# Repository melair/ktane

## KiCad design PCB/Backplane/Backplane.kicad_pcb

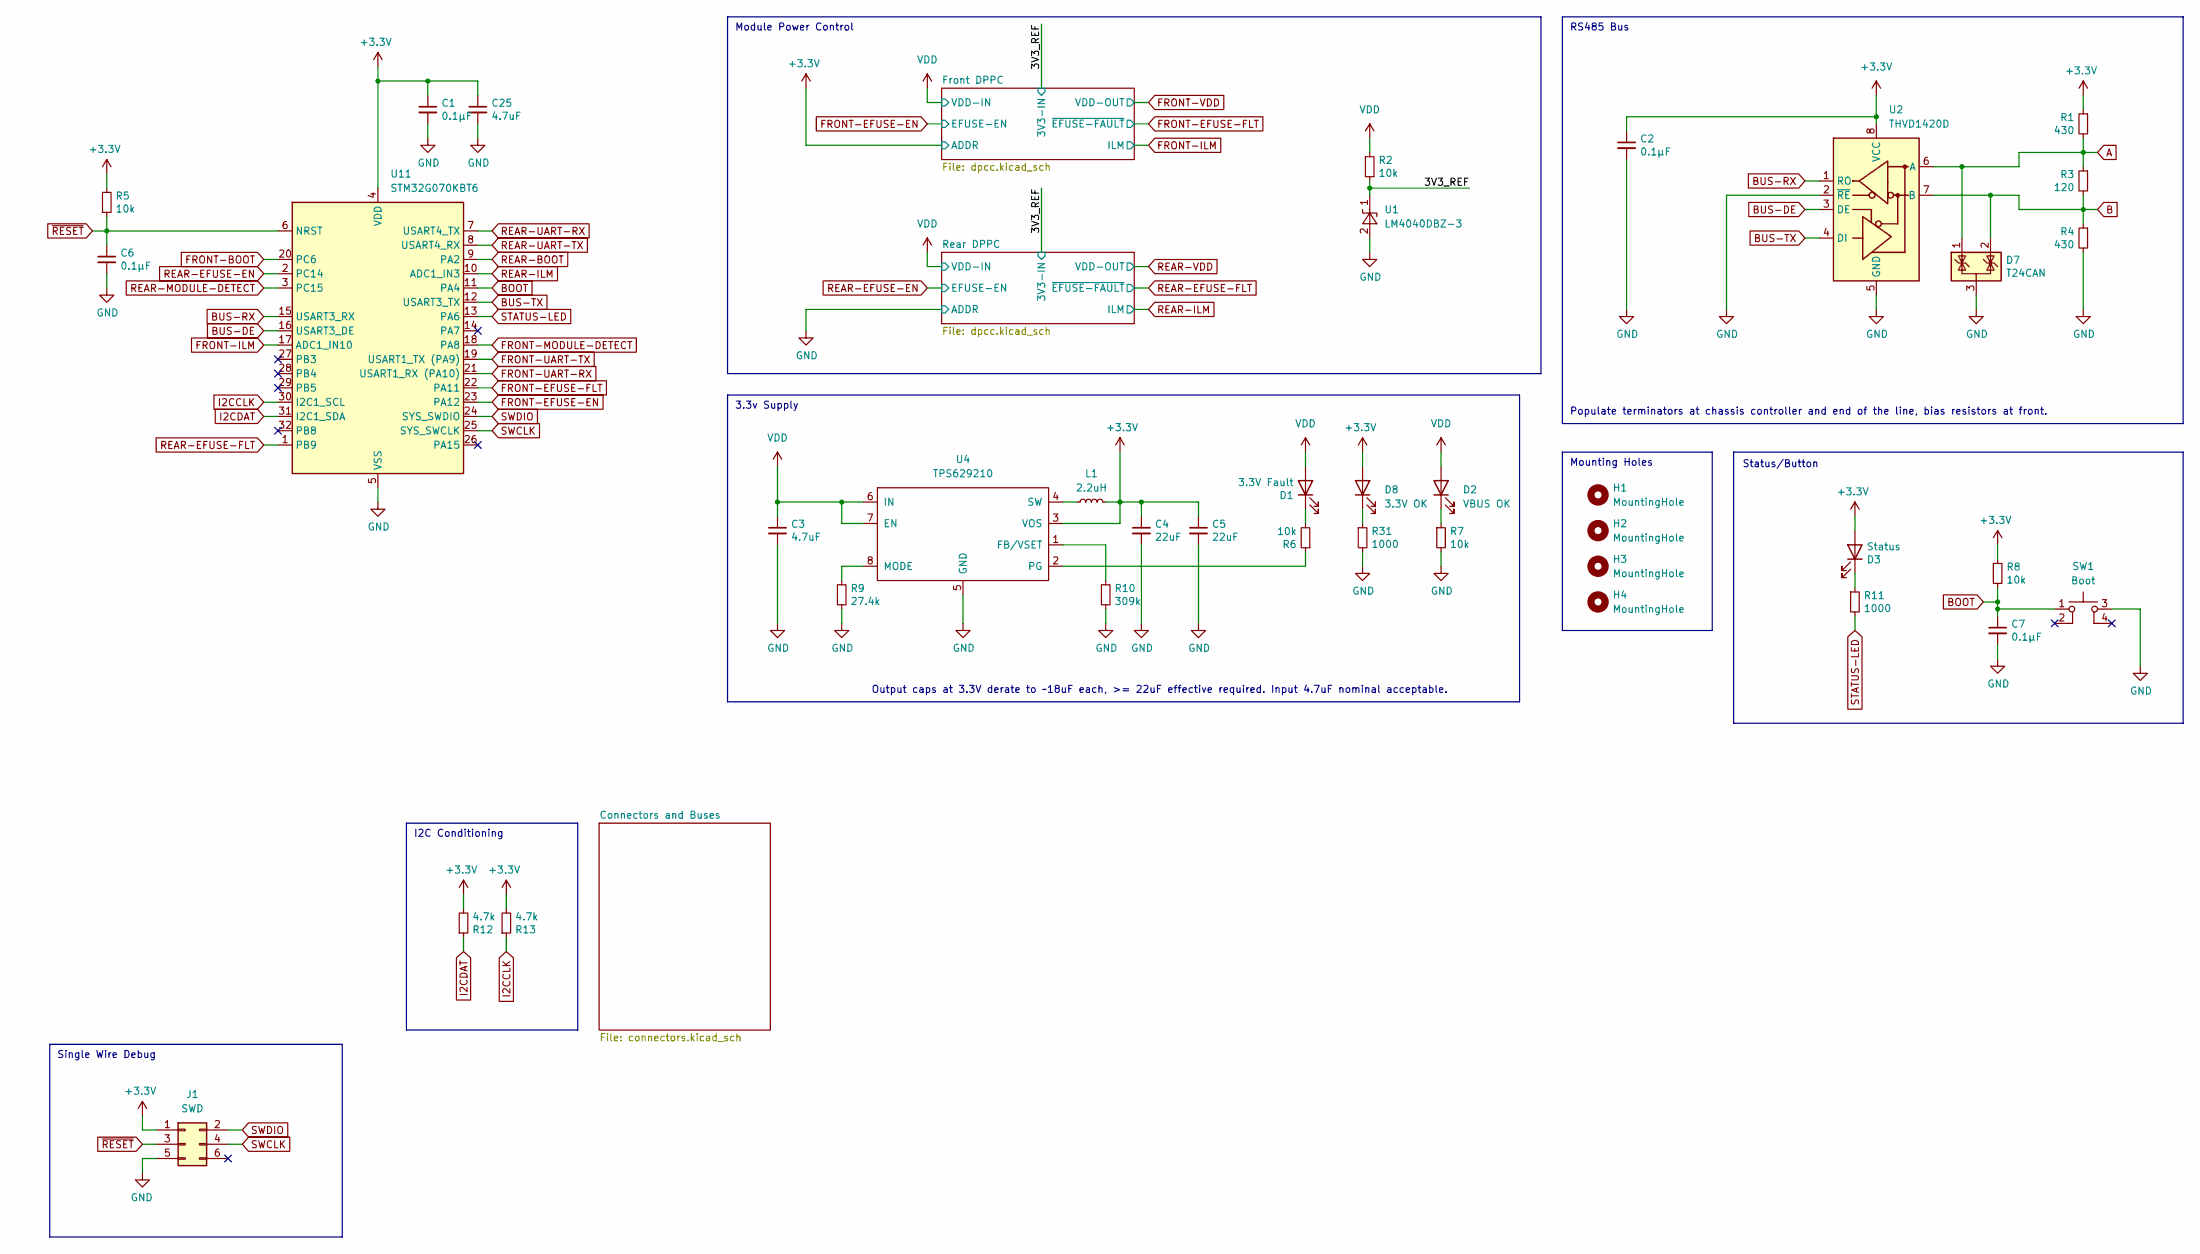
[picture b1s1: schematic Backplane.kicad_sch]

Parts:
C1, C2, C6, C7: 0.1μF; C_0603_1608Metric; DIGIKEY 1276-1005-1-ND
C3: 4.7uF; C_1206_3216Metric; DIGIKEY 445-1606-1-ND
C4, C5: 22uF; C_1206_3216Metric; DIGIKEY 1276-3148-1-ND
C25: 4.7uF; C_0603_1608Metric; DIGIKEY 1276-2087-1-ND
D1: 3.3V Fault; LED_0603_1608Metric; DIGIKEY 3147-B19Y1USD-20C000113U1930CT-ND
D2: VBUS OK; LED_0603_1608Metric; DIGIKEY 3147-B19Y1USD-20C000113U1930CT-ND
D3: Status; LED_0603_1608Metric; DIGIKEY 3147-B19Y1UYG-20C000313U1930CT-ND
D7: T24CAN; SOT-23; DIGIKEY CDSOT23-T24CANCT-ND
D8: 3.3V OK; LED_0603_1608Metric; DIGIKEY 3147-B19Y1UYG-20C000313U1930CT-ND
H1, H2, H3, H4: MountingHole; MountingHole_3.2mm_M3_NoCopper; DIGIKEY NONE
J1: SWD; Tag-Connect_TC2030-IDC-NL_2x03_P1.27mm_Vertical; DIGIKEY NONE
L1: 2.2uH; L_1008_2520Metric; DIGIKEY 490-DFE252012PD-2R2M=P2CT-ND
R1, R4: 430; R_0603_1608Metric; DIGIKEY P430HCT-ND
R2, R5, R6, R7, R8: 10k; R_0603_1608Metric; DIGIKEY P10.0KHCT-ND
R3: 120; R_0603_1608Metric; DIGIKEY P120HCT-ND
R9: 27.4k; R_0603_1608Metric; DIGIKEY P27.4KHCT-ND
R10: 309k; R_0603_1608Metric; DIGIKEY P309KHCT-ND
R11: 1000; R_0603_1608Metric; DIGIKEY P1.00KHCT-ND
R12, R13: 4.7k; R_0603_1608Metric; DIGIKEY P4.7KHCT-ND
R31: 1000; R_0603_1608Metric; DIGIKEY P1.0KHCT-ND
SW1: Boot; PTS526Sx15SMTR2xLFS; DIGIKEY CKN12220-1-ND
U1: LM4040DBZ-3; SOT-23; DIGIKEY 31-LM4040C33FTACT-ND
U2: THVD1420D; SOT-583-8; DIGIKEY 296-THVD1420DRLRCT-ND
U4: TPS629210; SOT-583-8; DIGIKEY 296-TPS629210DRLRCT-ND
U11: STM32G070KBT6; LQFP-32_7x7mm_P0.8mm; DIGIKEY 497-STM32G070KBT6-ND

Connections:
+3.3V: C1.1, C2.1, C4.1, C5.1, C25.1, D3.2 (A), D8.2 (A), J1.1, L1.2, R1.1, R5.1, R8.1, R12.2, R13.2, U2.8 (VCC), U4.3 (VOS), U11.4 (VDD); also elsewhere on the board
/3V3_REF: R2.2, U1.1 (K); also elsewhere on the board
A: D7.1 (K), R1.2, R3.1, U2.6 (A); also elsewhere on the board
B: D7.2 (K), R3.2, R4.1, U2.7 (B); also elsewhere on the board
BOOT: C7.1, R8.2, SW1.1, U11.11 (PA4)
BUS-DE: U2.3 (DE), U11.16 (USART3_DE)
BUS-RX: U2.1 (RO), U11.15 (USART3_RX)
BUS-TX: U2.4 (DI), U11.12 (USART3_TX)
FRONT-BOOT: U11.20 (PC6); also elsewhere on the board
FRONT-EFUSE-EN: U11.23 (PA12); also elsewhere on the board
FRONT-EFUSE-FLT: U11.22 (PA11); also elsewhere on the board
FRONT-ILM: U11.17 (ADC1_IN10); also elsewhere on the board
FRONT-MODULE-DETECT: U11.18 (PA8); also elsewhere on the board
FRONT-UART-RX: U11.21 (USART1_RX (PA10)); also elsewhere on the board
FRONT-UART-TX: U11.19 (USART1_TX (PA9)); also elsewhere on the board
GND: C1.2, C2.2, C3.2, C4.2, C5.2, C6.2, C7.2, C25.2, D7.3 (A), J1.5, R4.2, R7.2, R9.2, R10.2, R31.2, SW1.3, U1.2 (A), U2.2 (~RE), U2.5 (GND), U4.5 (GND), U11.5 (VSS); also elsewhere on the board
I2CCLK: R13.1, U11.30 (I2C1_SCL); also elsewhere on the board
I2CDAT: R12.1, U11.31 (I2C1_SDA); also elsewhere on the board
unnamed: D1.1 (K), R6.2
unnamed: D2.1 (K), R7.1
unnamed: D3.1 (K), R11.1
unnamed: D8.1 (K), R31.1
unnamed: R10.1, U4.1 (FB/VSET)
unnamed: R9.1, U4.8 (MODE)
unnamed: R6.1, U4.2 (PG)
unnamed: L1.1, U4.4 (SW)
REAR-BOOT: U11.9 (PA2); also elsewhere on the board
REAR-EFUSE-EN: U11.2 (PC14); also elsewhere on the board
REAR-EFUSE-FLT: U11.1 (PB9); also elsewhere on the board
REAR-ILM: U11.10 (ADC1_IN3); also elsewhere on the board
REAR-MODULE-DETECT: U11.3 (PC15); also elsewhere on the board
REAR-UART-RX: U11.7 (USART4_TX); also elsewhere on the board
REAR-UART-TX: U11.8 (USART4_RX); also elsewhere on the board
STATUS-LED: R11.2, U11.13 (PA6)
SWCLK: J1.4, U11.25 (SYS_SWCLK)
SWDIO: J1.2, U11.24 (SYS_SWDIO)
VDD: C3.1, D1.2 (A), D2.2 (A), R2.1, U4.6 (IN), U4.7 (EN); also elsewhere on the board
~RESET: C6.1, J1.3, R5.2, U11.6 (NRST)

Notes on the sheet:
I2C Conditioning
Module Power Control
Single Wire Debug
Output caps at 3.3V derate to ~18uF each, >= 22uF effective required. Input 4.7uF nominal acceptable.
Status/Button
Mounting Holes
3.3v Supply
Populate terminators at chassis controller and end of the line, bias resistors at front.
RS485 Bus

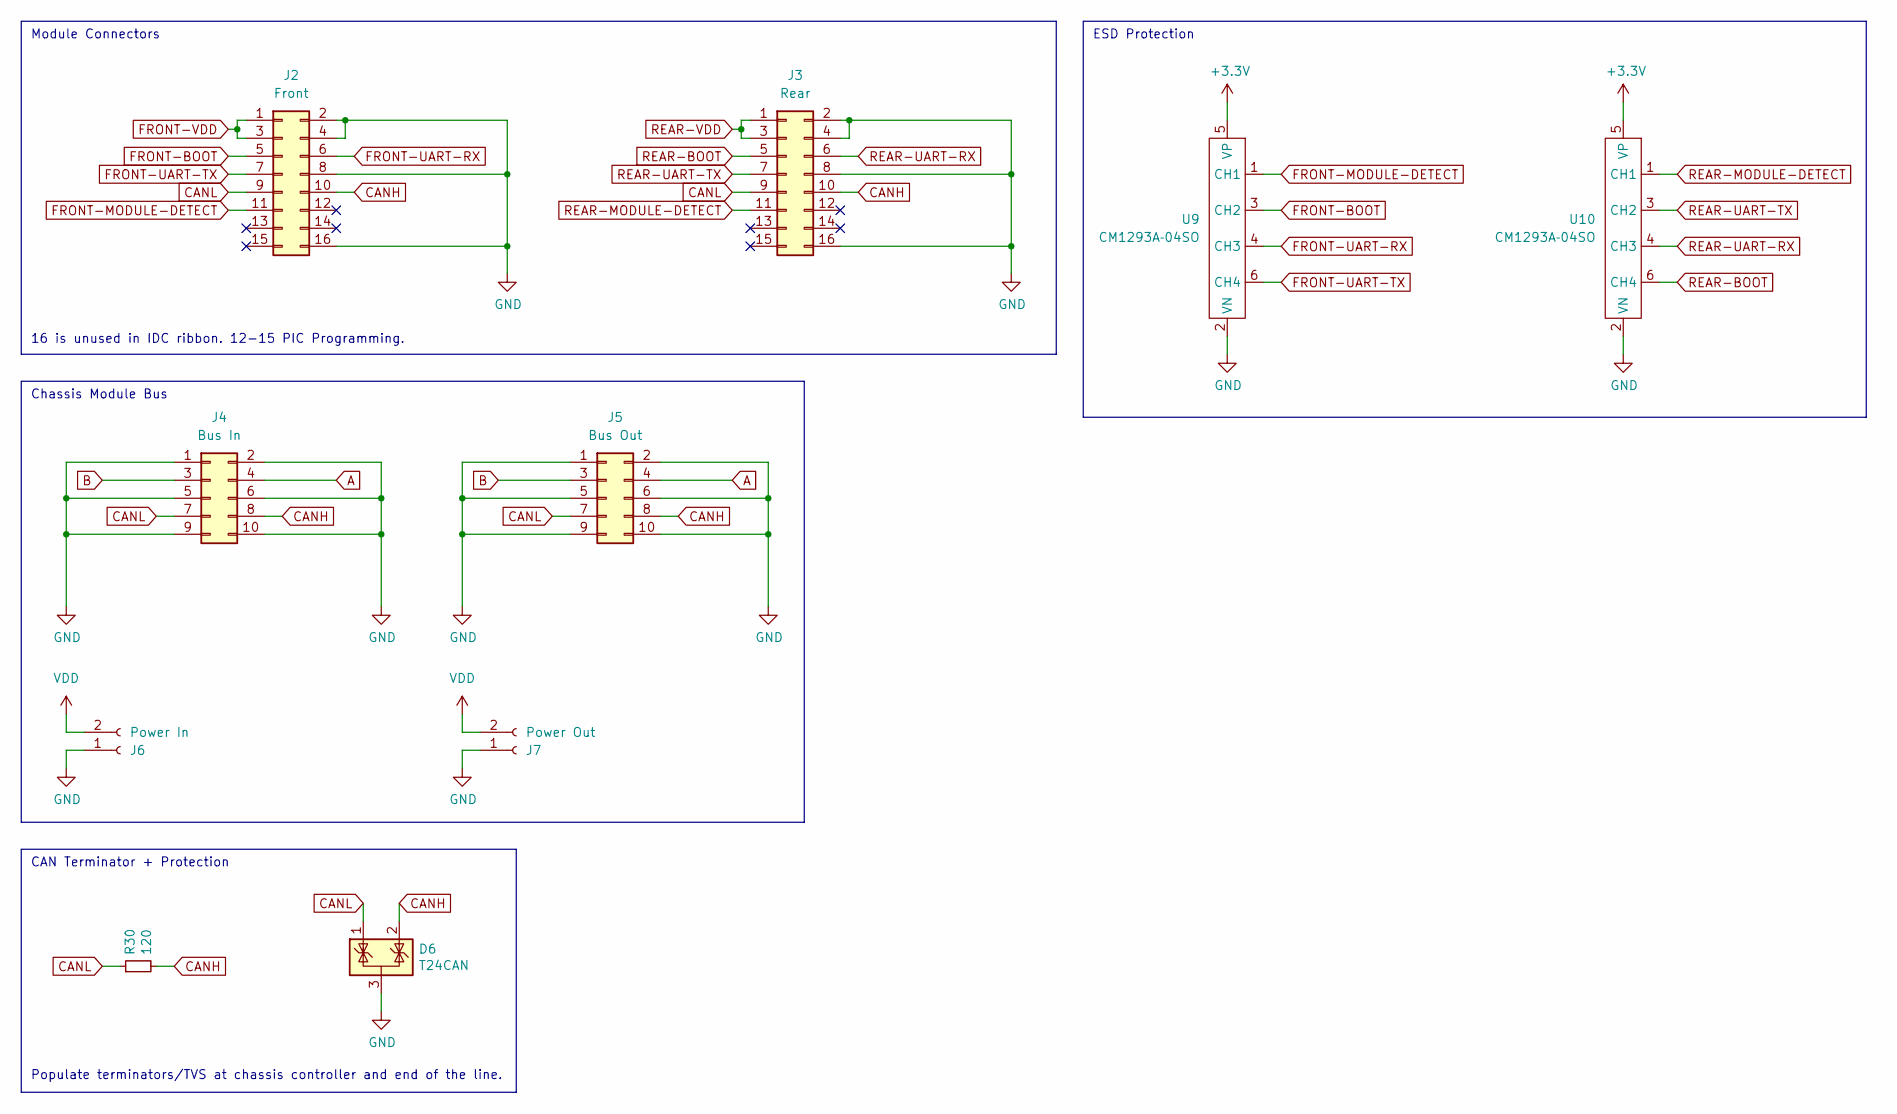
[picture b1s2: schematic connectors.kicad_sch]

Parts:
D6: T24CAN; SOT-23; DIGIKEY CDSOT23-T24CANCT-ND
J2: Front; PinHeader_2x08_P2.54mm_VerticalAndHorizontal_Centered; DIGIKEY STOCK/Toby
J3: Rear; PinHeader_2x08_P2.54mm_VerticalAndHorizontal_Centered; DIGIKEY STOCK/Toby
J4: Bus In; PinHeader_2x05_P2.54mm_VerticalAndHorizontal_Centered; DIGIKEY STOCK/Toby
J5: Bus Out; PinHeader_2x05_P2.54mm_VerticalAndHorizontal_Centered; DIGIKEY STOCK/Toby
J6: Power In; AMASS_XT30PW-M_1x02_P2.50mm_Horizontal; DIGIKEY STOCK/ALIEXPRESS
J7: Power Out; AMASS_XT30PW-F_1x02_P2.50mm_Horizontal; DIGIKEY STOCK/ALIEXPRESS
R30: 120; R_0603_1608Metric; DIGIKEY P120HCT-ND
U9, U10: CM1293A‐04SO; SC-74-6_1.55x2.9mm_P0.95mm; DIGIKEY CM1293A-04SOOSCT-ND

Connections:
+3.3V: U9.5 (VP), U10.5 (VP); also elsewhere on the board
A: J4.4, J5.4; also elsewhere on the board
B: J4.3, J5.3; also elsewhere on the board
CANH: D6.2 (K), J2.10, J3.10, J4.8, J5.8, R30.2
CANL: D6.1 (K), J2.9, J3.9, J4.7, J5.7, R30.1
FRONT-BOOT: J2.5, U9.3 (CH2); also elsewhere on the board
FRONT-MODULE-DETECT: J2.11, U9.1 (CH1); also elsewhere on the board
FRONT-UART-RX: J2.6, U9.4 (CH3); also elsewhere on the board
FRONT-UART-TX: J2.7, U9.6 (CH4); also elsewhere on the board
FRONT-VDD: J2.1, J2.3; also elsewhere on the board
GND: D6.3 (A), J2.2, J2.4, J2.8, J2.16, J3.2, J3.4, J3.8, J3.16, J4.1, J4.2, J4.5, J4.6, J4.9, J4.10, J5.1, J5.2, J5.5, J5.6, J5.9, J5.10, J6.1, J7.1, U9.2 (VN), U10.2 (VN); also elsewhere on the board
REAR-BOOT: J3.5, U10.6 (CH4); also elsewhere on the board
REAR-MODULE-DETECT: J3.11, U10.1 (CH1); also elsewhere on the board
REAR-UART-RX: J3.6, U10.4 (CH3); also elsewhere on the board
REAR-UART-TX: J3.7, U10.3 (CH2); also elsewhere on the board
REAR-VDD: J3.1, J3.3; also elsewhere on the board
VDD: J6.2, J7.2; also elsewhere on the board

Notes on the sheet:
Chassis Module Bus
Module Connectors
CAN Terminator + Protection
16 is unused in IDC ribbon. 12-15 PIC Programming.
Populate terminators/TVS at chassis controller and end of the line.
ESD Protection

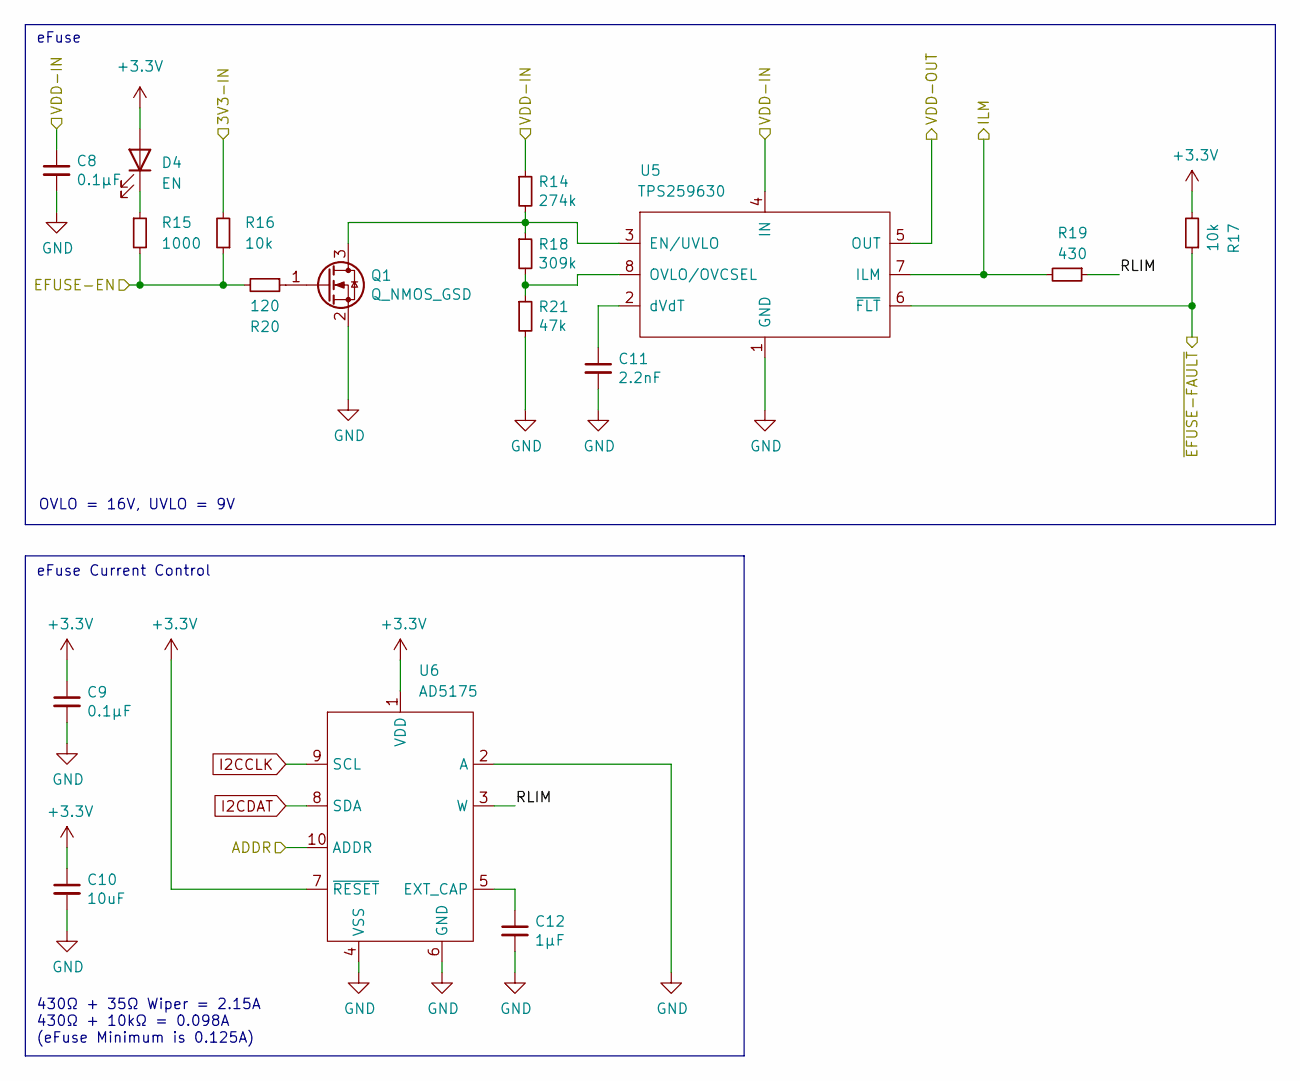
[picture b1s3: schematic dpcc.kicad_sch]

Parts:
C8, C9: 0.1μF; C_0603_1608Metric; DIGIKEY 1276-1005-1-ND
C10: 10uF; C_0603_1608Metric; DIGIKEY 1276-1948-1-ND
C11: 2.2nF; C_0603_1608Metric; DIGIKEY 1276-6530-1-ND
C12: 1μF; C_0603_1608Metric; DIGIKEY 1276-1946-1-ND
D4: EN; LED_0603_1608Metric; DIGIKEY 3147-B19Y1USD-20C000113U1930CT-ND
Q1: Q_NMOS_GSD; SOT-23; DIGIKEY 31-DMN2310U-7CT-ND
R14: 274k; R_0603_1608Metric; DIGIKEY P274KHCT-ND
R15: 1000; R_0603_1608Metric; DIGIKEY P1.00KHCT-ND
R16, R17: 10k; R_0603_1608Metric; DIGIKEY P10.0KHCT-ND
R18: 309k; R_0603_1608Metric; DIGIKEY P309KHCT-ND
R19: 430; R_0603_1608Metric; DIGIKEY P430HCT-ND
R20: 120; R_0603_1608Metric; DIGIKEY P120HCT-ND
R21: 47k; R_0603_1608Metric; DIGIKEY P47.0KHCT-ND
U5: TPS259630; SOIC-8-1EP_3.9x4.9mm_P1.27mm_EP2.29x3mm; DIGIKEY 296-TPS259631DDARCT-ND
U6: AD5175; MSOP-10_3x3mm_P0.5mm; DIGIKEY 505-AD5175BRMZ-10-ND

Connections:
+3.3V: C9.1, C10.1, D4.2 (A), R17.2, U6.1 (VDD), U6.7 (~RESET), U6.10 (ADDR); also elsewhere on the board
/3V3_REF: R16.2; also elsewhere on the board
/Front DPPC/RLIM: R19.1, U6.3 (W)
FRONT-EFUSE-EN: R15.2, R16.1, R20.2; also elsewhere on the board
FRONT-EFUSE-FLT: R17.1, U5.6 (~FLT); also elsewhere on the board
FRONT-ILM: R19.2, U5.7 (ILM); also elsewhere on the board
FRONT-VDD: U5.5 (OUT); also elsewhere on the board
GND: C8.2, C9.2, C10.2, C11.2, C12.2, Q1.2 (S), R21.2, U5.1 (GND), U5.9 (GND), U6.2 (A), U6.4 (VSS), U6.6 (GND); also elsewhere on the board
I2CCLK: U6.9 (SCL); also elsewhere on the board
I2CDAT: U6.8 (SDA); also elsewhere on the board
unnamed: D4.1 (K), R15.1
unnamed: Q1.3 (D), R14.2, R18.1, U5.3 (EN/UVLO)
unnamed: Q1.1 (G), R20.1
unnamed: R18.2, R21.1, U5.8 (OVLO/OVCSEL)
unnamed: C11.1, U5.2 (dVdT)
unnamed: C12.1, U6.5 (EXT_CAP)
VDD: C8.1, R14.1, U5.4 (IN); also elsewhere on the board

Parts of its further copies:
C13, C14: 0.1μF; C_0603_1608Metric; DIGIKEY 1276-1005-1-ND
C15: 10uF; C_0603_1608Metric; DIGIKEY 1276-1948-1-ND
C16: 2.2nF; C_0603_1608Metric; DIGIKEY 1276-6530-1-ND
C17: 1μF; C_0603_1608Metric; DIGIKEY 1276-1946-1-ND
D5: EN; LED_0603_1608Metric; DIGIKEY 3147-B19Y1USD-20C000113U1930CT-ND
Q2: Q_NMOS_GSD; SOT-23; DIGIKEY 31-DMN2310U-7CT-ND
R22: 274k; R_0603_1608Metric; DIGIKEY P274KHCT-ND
R23: 1000; R_0603_1608Metric; DIGIKEY P1.00KHCT-ND
R24, R25: 10k; R_0603_1608Metric; DIGIKEY P10.0KHCT-ND
R26: 309k; R_0603_1608Metric; DIGIKEY P309KHCT-ND
R27: 430; R_0603_1608Metric; DIGIKEY P430HCT-ND
R28: 120; R_0603_1608Metric; DIGIKEY P120HCT-ND
R29: 47k; R_0603_1608Metric; DIGIKEY P47.0KHCT-ND
U7: TPS259630; SOIC-8-1EP_3.9x4.9mm_P1.27mm_EP2.29x3mm; DIGIKEY 296-TPS259631DDARCT-ND
U8: AD5175; MSOP-10_3x3mm_P0.5mm; DIGIKEY 505-AD5175BRMZ-10-ND

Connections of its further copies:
+3.3V: C14.1, C15.1, D5.2 (A), R25.2, U8.1 (VDD), U8.7 (~RESET); also elsewhere on the board
/3V3_REF: R24.2; also elsewhere on the board
/Rear DPPC/RLIM: R27.1, U8.3 (W)
GND: C13.2, C14.2, C15.2, C16.2, C17.2, Q2.2 (S), R29.2, U7.1 (GND), U7.9 (GND), U8.2 (A), U8.4 (VSS), U8.6 (GND), U8.10 (ADDR); also elsewhere on the board
I2CCLK: U8.9 (SCL); also elsewhere on the board
I2CDAT: U8.8 (SDA); also elsewhere on the board
unnamed: D5.1 (K), R23.1
unnamed: Q2.3 (D), R22.2, R26.1, U7.3 (EN/UVLO)
unnamed: Q2.1 (G), R28.1
unnamed: R26.2, R29.1, U7.8 (OVLO/OVCSEL)
unnamed: C16.1, U7.2 (dVdT)
unnamed: C17.1, U8.5 (EXT_CAP)
REAR-EFUSE-EN: R23.2, R24.1, R28.2; also elsewhere on the board
REAR-EFUSE-FLT: R25.1, U7.6 (~FLT); also elsewhere on the board
REAR-ILM: R27.2, U7.7 (ILM); also elsewhere on the board
REAR-VDD: U7.5 (OUT); also elsewhere on the board
VDD: C13.1, R22.1, U7.4 (IN); also elsewhere on the board

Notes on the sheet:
eFuse
430Ω + 35Ω Wiper = 2.15A 430Ω + 10kΩ = 0.098A (eFuse Minimum is 0.125A)
OVLO = 16V, UVLO = 9V
eFuse Current Control

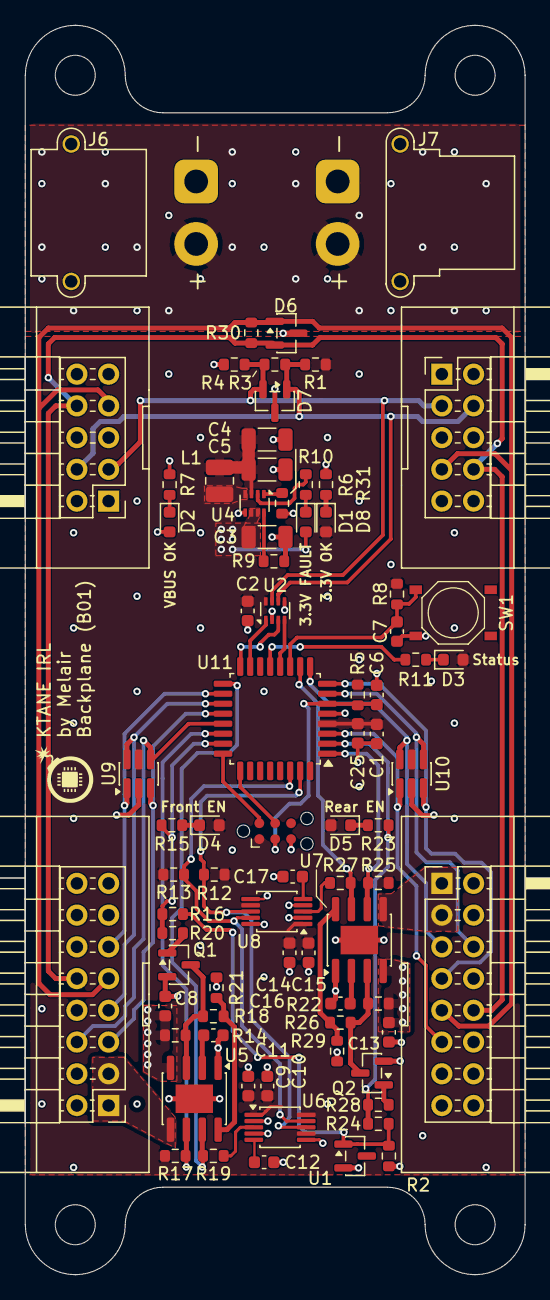
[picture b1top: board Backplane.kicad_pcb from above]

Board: 4 copper layers, 40.0 x 100.0 mm, 82 parts (0 on the bottom side), 56 nets.

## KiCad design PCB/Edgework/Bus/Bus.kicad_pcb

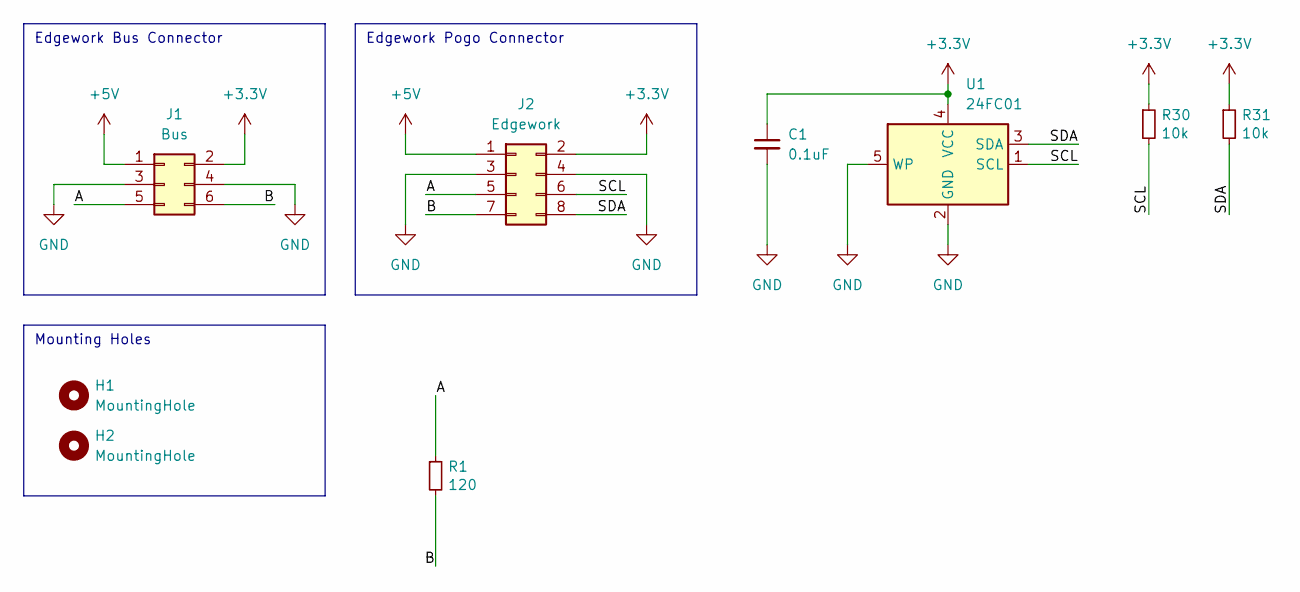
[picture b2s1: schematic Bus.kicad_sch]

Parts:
C1: 0.1uF; C_0603_1608Metric; DIGIKEY 1276-1005-1-ND
H1, H2: MountingHole; MountingHole_3.2mm_M3; DIGIKEY NONE
J1: Bus; PinHeader_2x03_P2.54mm_Horizontal; DIGIKEY STOCK
J2: Edgework; PinHeader_2x04_P2.54mm_Vertical; DIGIKEY STOCK
R1: 120; R_0603_1608Metric; DIGIKEY P120HCT-ND
R30, R31: 10k; R_0603_1608Metric; DIGIKEY P10.0KHCT-ND
U1: 24FC01; SOT-23-5; DIGIKEY 24FC01T-I/OTCT-ND

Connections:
+3.3V: C1.1, J1.2, J2.2, R30.1, R31.1, U1.4 (VCC)
+5V: J1.1, J2.1
/A: J1.5, J2.5, R1.1
/B: J1.6, J2.7, R1.2
/SCL: J2.6, R30.2, U1.1 (SCL)
/SDA: J2.8, R31.2, U1.3 (SDA)
GND: C1.2, J1.3, J1.4, J2.3, J2.4, U1.2 (GND), U1.5 (WP)

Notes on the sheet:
Edgework Bus Connector
Edgework Pogo Connector
Mounting Holes

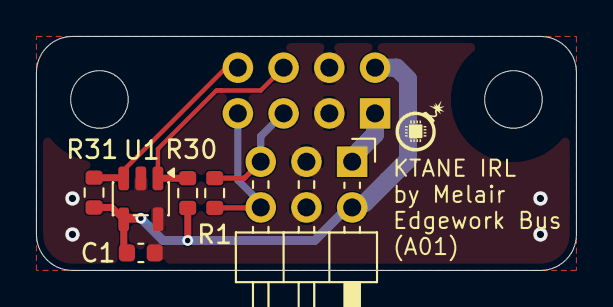
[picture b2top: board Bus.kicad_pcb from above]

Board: 2 copper layers, 30.0 x 13.0 mm, 9 parts (1 on the bottom side), 7 nets.

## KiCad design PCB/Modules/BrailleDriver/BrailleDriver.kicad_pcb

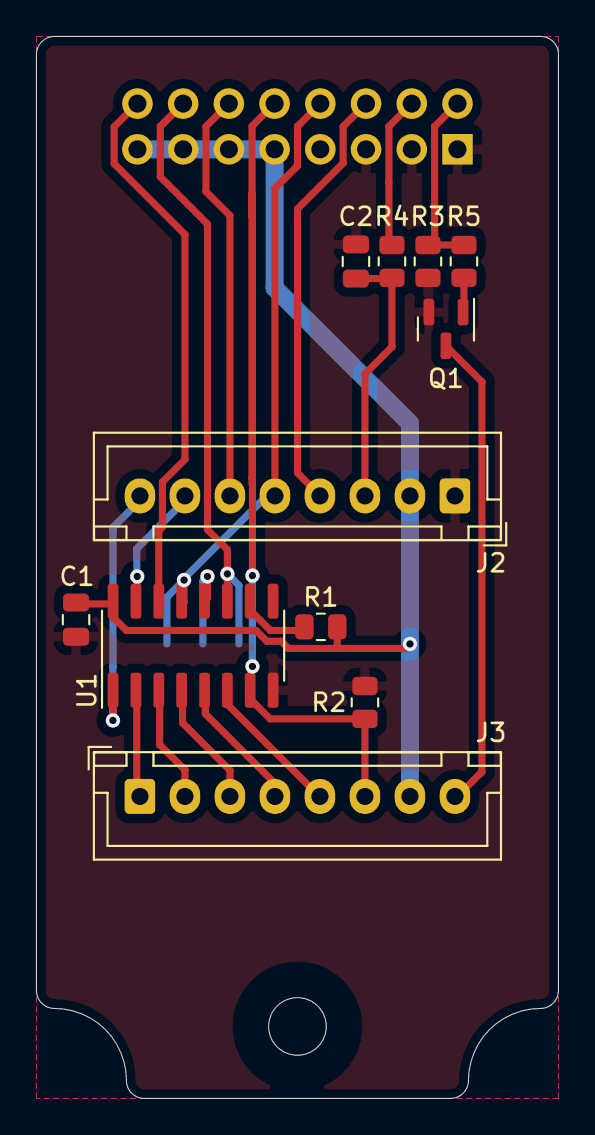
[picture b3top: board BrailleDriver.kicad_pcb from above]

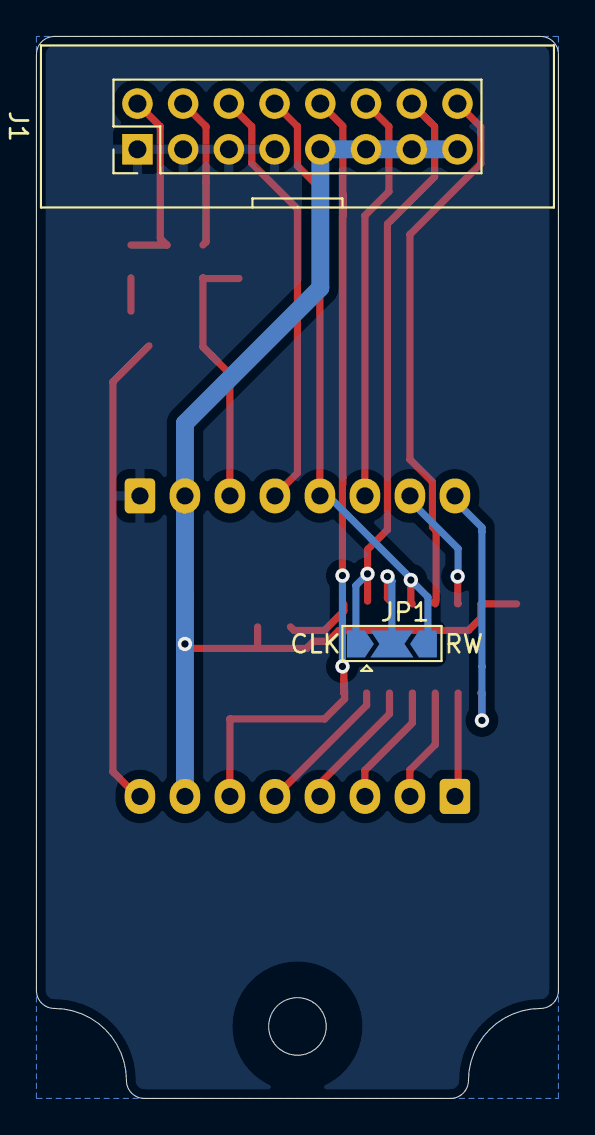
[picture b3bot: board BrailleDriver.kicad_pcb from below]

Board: 2 copper layers, 29.0 x 59.0 mm, 13 parts (2 on the bottom side), 22 nets.

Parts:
C1: 10uF; C_0805_2012Metric
C2: 22uF; C_0805_2012Metric
J1: In; PinHeader_2x08_P2.54mm_Vertical-Centered
J2, J3: Conn_01x08; JST_XH_B8B-XH-A_1x08_P2.50mm_Vertical
JP1: Jumper_3_Open; SolderJumper-3_P2.0mm_Open_TrianglePad1.0x1.5mm
Q1: Q_NMOS_GSD; SOT-23
R1, R2: 10k; R_0805_2012Metric
R3: 47k; R_0805_2012Metric
R4: 1k; R_0805_2012Metric
R5: 120; R_0805_2012Metric
U1: 74HC595; SOIC-16_3.9x9.9mm_P1.27mm

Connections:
+5V: C1.1, J1.9, J1.11, J1.13, J1.15, J2.2, J3.7, R1.2, U1.16 (VCC)
/D0: J2.7, U1.15 (QA)
/D1: J2.8, U1.1 (QB)
/D2: J3.1, U1.2 (QC)
/D3: J3.2, U1.3 (QD)
/D4: J3.3, U1.4 (QE)
/D5: J3.4, U1.5 (QF)
/D6: J3.5, U1.6 (QG)
CLK: J1.14, JP1.1 (A), U1.11 (SRCLK)
D7: J1.10, J3.6, R2.2, U1.7 (QH)
DAT: J1.16, U1.14 (SER)
E: J1.12, J2.6
GND: C1.2, C2.2, J1.1, J1.3, J1.5, J1.7, J2.1, Q1.2 (S), R2.1, R3.1, U1.8 (GND)
K: J3.8, Q1.3 (D)
K-SIGNAL: J1.2, R3.2, R5.2
unnamed: Q1.1 (G), R5.1
unnamed: R1.1, U1.10 (~SRCLR)
unnamed: JP1.2 (C), U1.12 (RCLK)
RS: J1.6, J2.4
RW: J1.8, J2.5, JP1.3 (B), U1.13 (~OE)
VO: C2.1, J2.3, R4.1
VO-SIGNAL: J1.4, R4.2

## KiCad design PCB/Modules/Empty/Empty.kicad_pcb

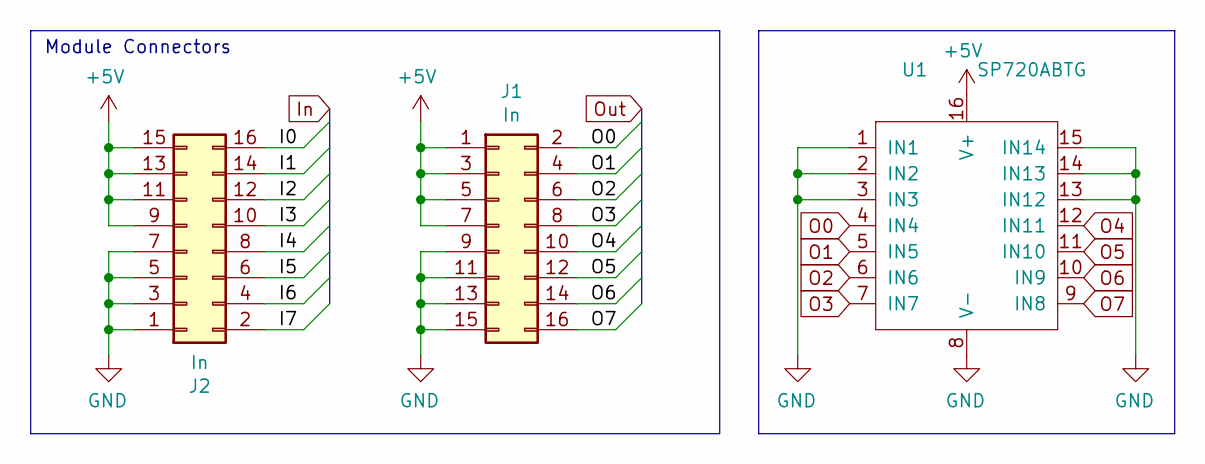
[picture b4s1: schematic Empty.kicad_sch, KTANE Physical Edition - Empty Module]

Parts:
J1, J2: In; PinHeader_2x08_P2.54mm_Vertical-Centered
U1: SP720ABTG; SOIC-16_3.9x9.9mm_P1.27mm

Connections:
+5V: J1.1, J1.3, J1.5, J1.7, J2.9, J2.11, J2.13, J2.15, U1.16 (V+)
GND: J1.9, J1.11, J1.13, J1.15, J2.1, J2.3, J2.5, J2.7, U1.1 (IN1), U1.2 (IN2), U1.3 (IN3), U1.8 (V-), U1.13 (IN12), U1.14 (IN13), U1.15 (IN14)
I0: J2.16
I1: J2.14
I2: J2.12
I3: J2.10
I4: J2.8
I5: J2.6
I6: J2.4
I7: J2.2
O0: J1.2, U1.4 (IN4)
O1: J1.4, U1.5 (IN5)
O2: J1.6, U1.6 (IN6)
O3: J1.8, U1.7 (IN7)
O4: J1.10, U1.12 (IN11)
O5: J1.12, U1.11 (IN10)
O6: J1.14, U1.10 (IN9)
O7: J1.16, U1.9 (IN8)

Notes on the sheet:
Module Connectors

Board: 2 copper layers, 3 parts (1 on the bottom side), 10 nets, no tracks yet.

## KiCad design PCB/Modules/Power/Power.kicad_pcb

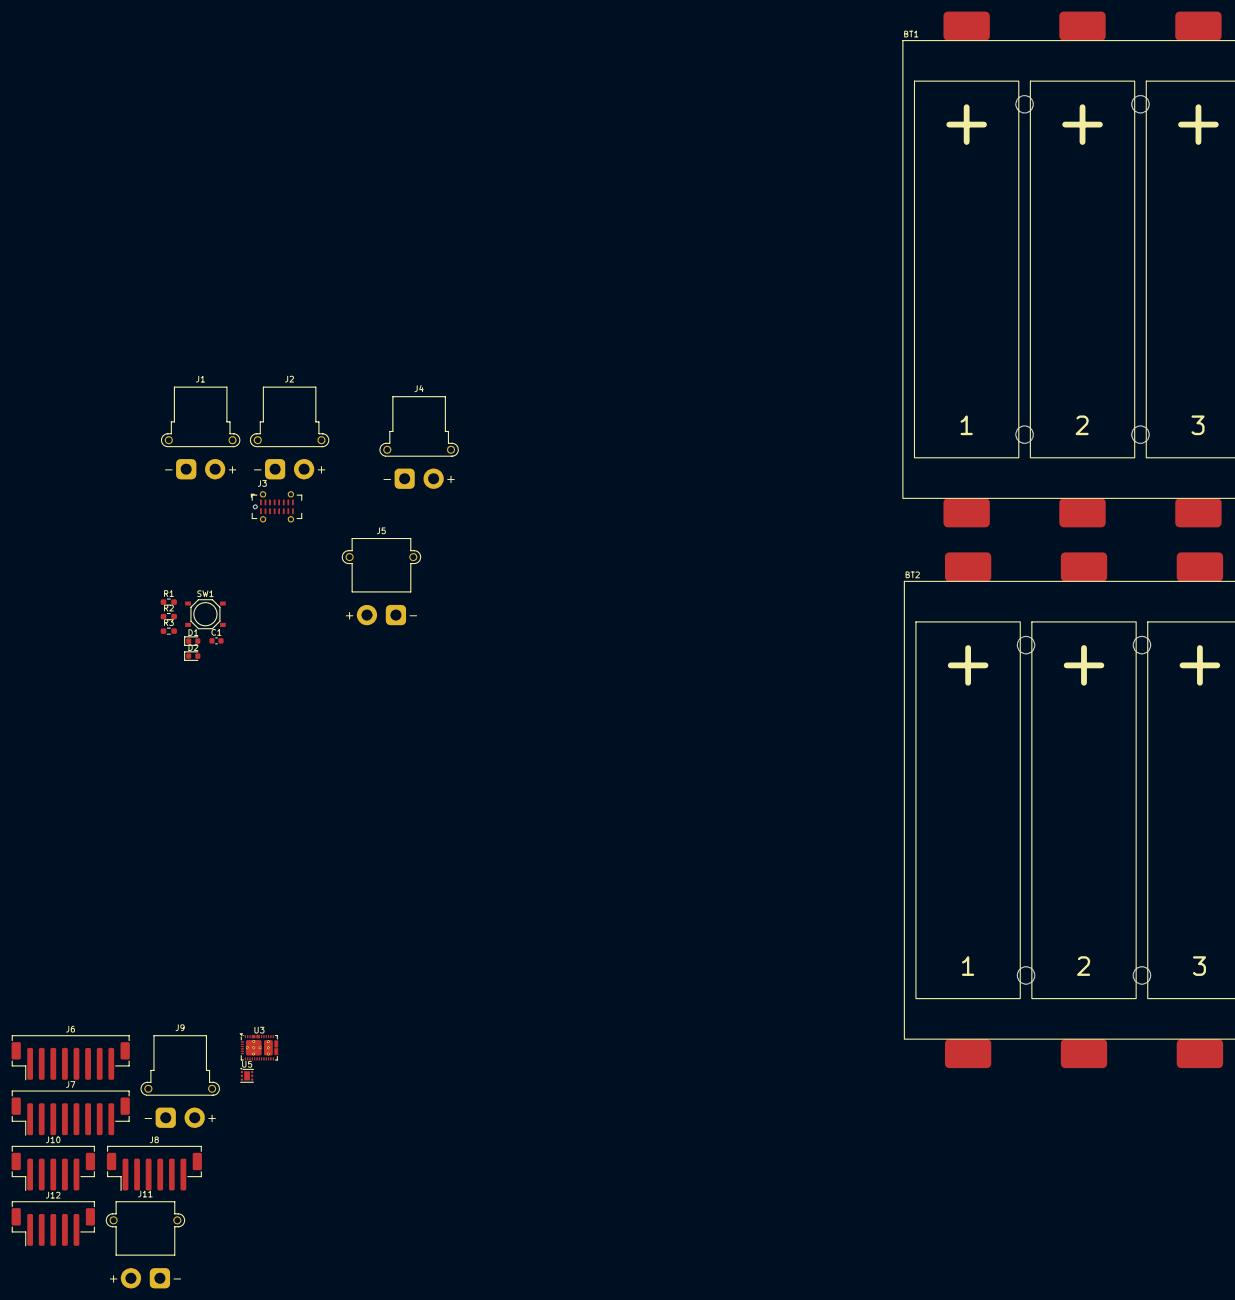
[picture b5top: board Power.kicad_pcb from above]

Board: 2 copper layers, 23 parts (0 on the bottom side), 27 nets, no tracks yet.

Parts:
BT1, BT2: 3Cell18650Holder
C1: 1nF; C_0603_1608Metric
D1: OK; LED_0603_1608Metric
D2: Fault; LED_0603_1608Metric
J1: Out1; AMASS_XT30PW-F_1x02_P2.50mm_Horizontal
J2: Out2; AMASS_XT30PW-F_1x02_P2.50mm_Horizontal
J3: USB_C_Receptacle_USB2.0_14P; USB_C_Receptacle_G-Switch_GT-USB-7051x
J4: VBus; AMASS_XT30PW-F_1x02_P2.50mm_Horizontal
J5: VBus; AMASS_XT30PW-M_1x02_P2.50mm_Horizontal
J6, J7: Comms; JST_PH_B8B-PH-SM4-TB_1x08-1MP_P2.00mm_Vertical
J8: Host; JST_PH_B6B-PH-SM4-TB_1x06-1MP_P2.00mm_Vertical
J9: Battery; AMASS_XT30PW-F_1x02_P2.50mm_Horizontal
J10, J12: Comms; JST_PH_B5B-PH-SM4-TB_1x05-1MP_P2.00mm_Vertical
J11: Battery; AMASS_XT30PW-M_1x02_P2.50mm_Horizontal
R1: 1M; R_0603_1608Metric_Pad0.98x0.95mm_HandSolder
R2, R3: 100; R_0603_1608Metric_Pad0.98x0.95mm_HandSolder
SW1: Action; PTS526Sx15SMTR2xLFS
U3: TPS25751D; Texas_REF0038A_WQFN-38-2EP_6x4mm_P0.4
U5: TVS2200DRV; WSON-6-1EP_2x2mm_P0.65mm_EP1x1.6mm

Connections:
/Battery/GND: J11.1, J12.5
/Interface/BUTTON: J6.5, SW1.2
/Interface/CC1: J3.A5 (CC1), J6.1
/Interface/CC2: J3.B5 (CC2), J6.2
/Interface/D+: J3.A6 (D+), J3.B6 (D+), J6.4
/Interface/D-: J3.A7 (D-), J3.B7 (D-), J6.3
/Interface/GND: C1.2, D1.1 (K), D2.1 (K), J3.A1 (GND), J3.A12 (GND), J3.B1 (GND), J3.B12 (GND), J4.1, J6.8, R1.1, SW1.1
/Interface/LED-GREEN: J6.6, R2.1
/Interface/LED-RED: J6.7, R3.2
/Interface/SHIELD: C1.1, J3.S1 (SHIELD), R1.2
/Interface/VBUS: J3.A4 (VBUS), J3.A9 (VBUS), J3.B4 (VBUS), J3.B9 (VBUS), J4.2
/Manager/CC1: J7.1, U3.28 (CC1)
/Manager/CC2: J7.2, U3.29 (CC2)
/Manager/OUT1: J1.2, J2.2
/Manager/SCL: J10.1, U3.9 (I2Ct_SCL)
/Manager/SDA: J10.2, U3.8 (I2Ct_SDA)
/Manager/~ALERT: J10.3, U3.10 (~I2Ct_IRQ)
GND: J1.1, J2.1, J5.1, J7.8, J8.6, J9.1, J10.4, J10.5, U3.5 (GPIO0), U3.6 (GPIO1), U3.7 (GPIO2), U3.11 (GND), U3.12 (GND), U3.13 (GPIO11), U3.14 (GND), U3.19 (GPIO3), U3.26 (GPIO4), U3.27 (GPIO5), U3.31 (GND), U3.34 (PP5V), U3.36 (GPIO7), U3.37 (GPIO6), U3.39 (GND), U5.1 (GND), U5.2 (GND), U5.3 (GND), U5.7 (GND)
unnamed: BT1.1 (+), BT2.1 (+)
unnamed: BT1.2 (-), BT1.3 (+), BT2.2 (-), BT2.3 (+)
unnamed: BT1.4 (-), BT1.5 (+), BT2.4 (-), BT2.5 (+)
unnamed: BT1.6 (-), BT2.6 (-)
unnamed: D1.2 (A), R2.2
unnamed: D2.2 (A), R3.1
unnamed: U3.1 (LDO_3V3), U3.2 (ACDIN1)
unnamed: U3.3 (ACDIN2), U3.4 (LDO_1V5)
VBUS_IN: J5.2, U3.23 (VBUS_IN), U3.32 (VBUS), U5.4 (IN), U5.5 (IN), U5.6 (IN)
